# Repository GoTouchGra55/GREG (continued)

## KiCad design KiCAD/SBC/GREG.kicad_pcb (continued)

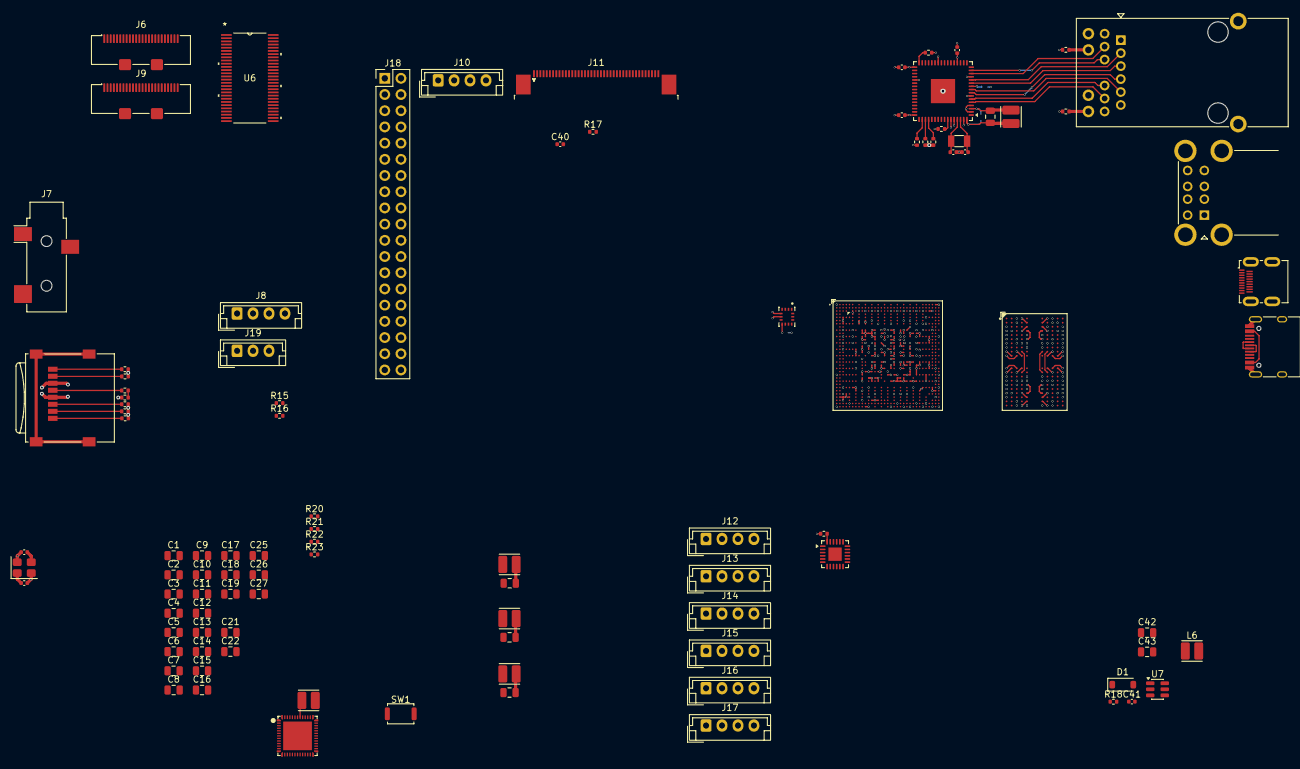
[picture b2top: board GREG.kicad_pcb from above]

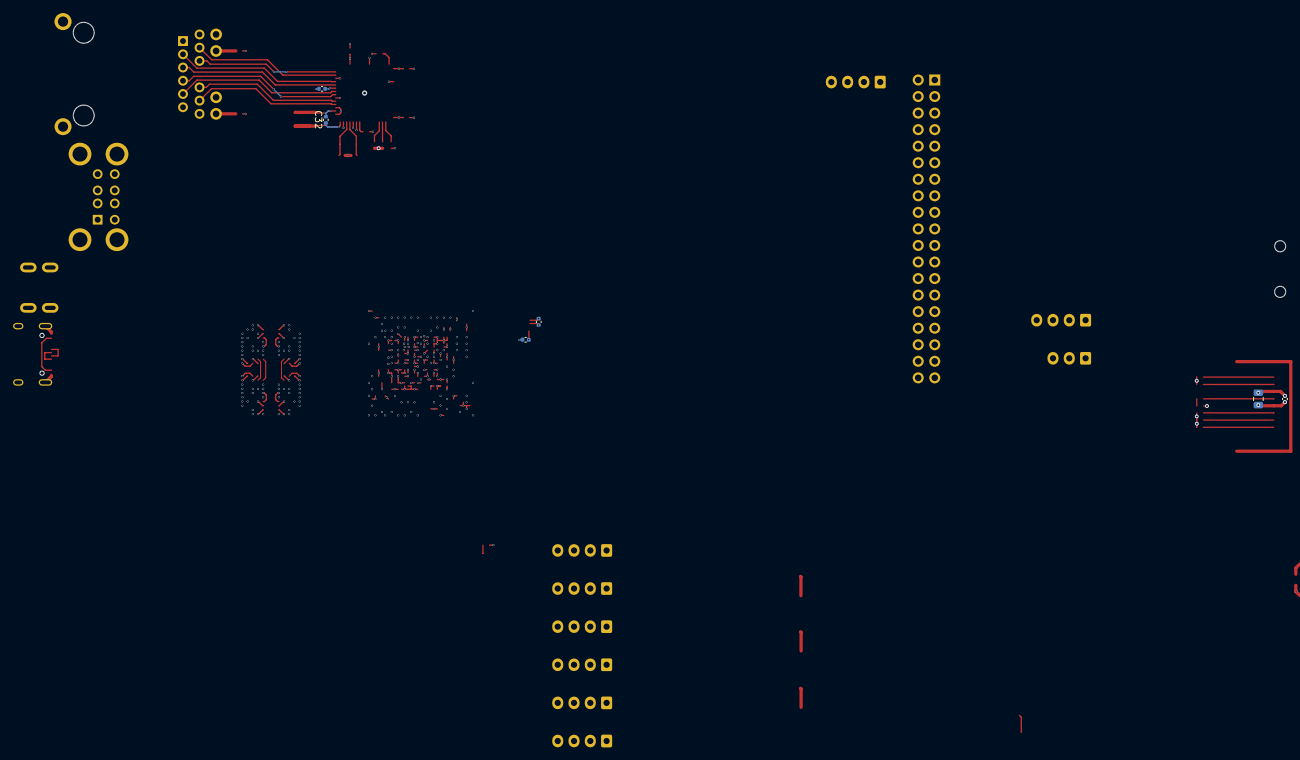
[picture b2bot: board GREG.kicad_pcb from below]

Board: 10 copper layers, 105 parts (6 on the bottom side), 293 nets.
